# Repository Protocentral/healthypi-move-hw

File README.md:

<div align="center">

</div>

# HealthyPi Move

HealthyPi Move is an open hardware device that lets you track all your vital signs to a high degree of accuracy. But it’s not just another smartwatch with a heart rate monitor. It is a complete vital signs monitoring and recording device on your wrist that can measure electrocardiogram (ECG), photoplethysmogram (PPG), SpO₂, blood pressure (finger-based), EDA/GSR, heart rate variability (HRV), respiration rate, and even body temperature.

The firmware for the HealthyPi Move is available at it's own repository - [HealthyPi Move Firmware](https://github.com/Protocentral/healthypi-move-fw)

HealthyPi Move is now available for pre-order in the ongoing campaign on [Crowd Supply](https://www.crowdsupply.com/protocentral/healthypi-move)

## Repository Contents

* **/pcbs** - All Eagle PCB design files (.brd, .sch)
* **/enclosure** - Enclosure design files

## License Information

This product is open source! Both, our hardware and software are open source and licensed under the following licenses:

Hardware
---------

**All hardware is released under the [CERN-OHL-P v2](https://ohwr.org/cern_ohl_p_v2.txt)** license.

Copyright CERN 2020.

This source describes Open Hardware and is licensed under the CERN-OHL-P v2.

You may redistribute and modify this documentation and make products
using it under the terms of the CERN-OHL-P v2 (https:/cern.ch/cern-ohl).
This documentation is distributed WITHOUT ANY EXPRESS OR IMPLIED
WARRANTY, INCLUDING OF MERCHANTABILITY, SATISFACTORY QUALITY
AND FITNESS FOR A PARTICULAR PURPOSE. Please see the CERN-OHL-P v2
for applicable conditions

Software
--------

**All software is released under the MIT License(http://opensource.org/licenses/MIT).**

THE SOFTWARE IS PROVIDED "AS IS", WITHOUT WARRANTY OF ANY KIND, EXPRESS OR IMPLIED, INCLUDING BUT NOT LIMITED TO THE WARRANTIES OF MERCHANTABILITY, FITNESS FOR A PARTICULAR PURPOSE AND NONINFRINGEMENT. IN NO EVENT SHALL THE AUTHORS OR COPYRIGHT HOLDERS BE LIABLE FOR ANY CLAIM, DAMAGES OR OTHER LIABILITY, WHETHER IN AN ACTION OF CONTRACT, TORT OR OTHERWISE, ARISING FROM, OUT OF OR IN CONNECTION WITH THE SOFTWARE OR THE USE OR OTHER DEALINGS IN THE SOFTWARE.

Documentation
-------------
**All documentation is released under [Creative Commons Share-alike 4.0 International](http://creativecommons.org/licenses/by-sa/4.0/).**

You are free to:

* Share — copy and redistribute the material in any medium or format
* Adapt — remix, transform, and build upon the material for any purpose, even commercially.
The licensor cannot revoke these freedoms as long as you follow the license terms.

Under the following terms:

* Attribution — You must give appropriate credit, provide a link to the license, and indicate if changes were made. You may do so in any reasonable manner, but not in any way that suggests the licensor endorses you or your use.
* ShareAlike — If you remix, transform, or build upon the material, you must distribute your contributions under the same license as the original.

Please check [*LICENSE.md*](LICENSE.md) for detailed license descriptions.

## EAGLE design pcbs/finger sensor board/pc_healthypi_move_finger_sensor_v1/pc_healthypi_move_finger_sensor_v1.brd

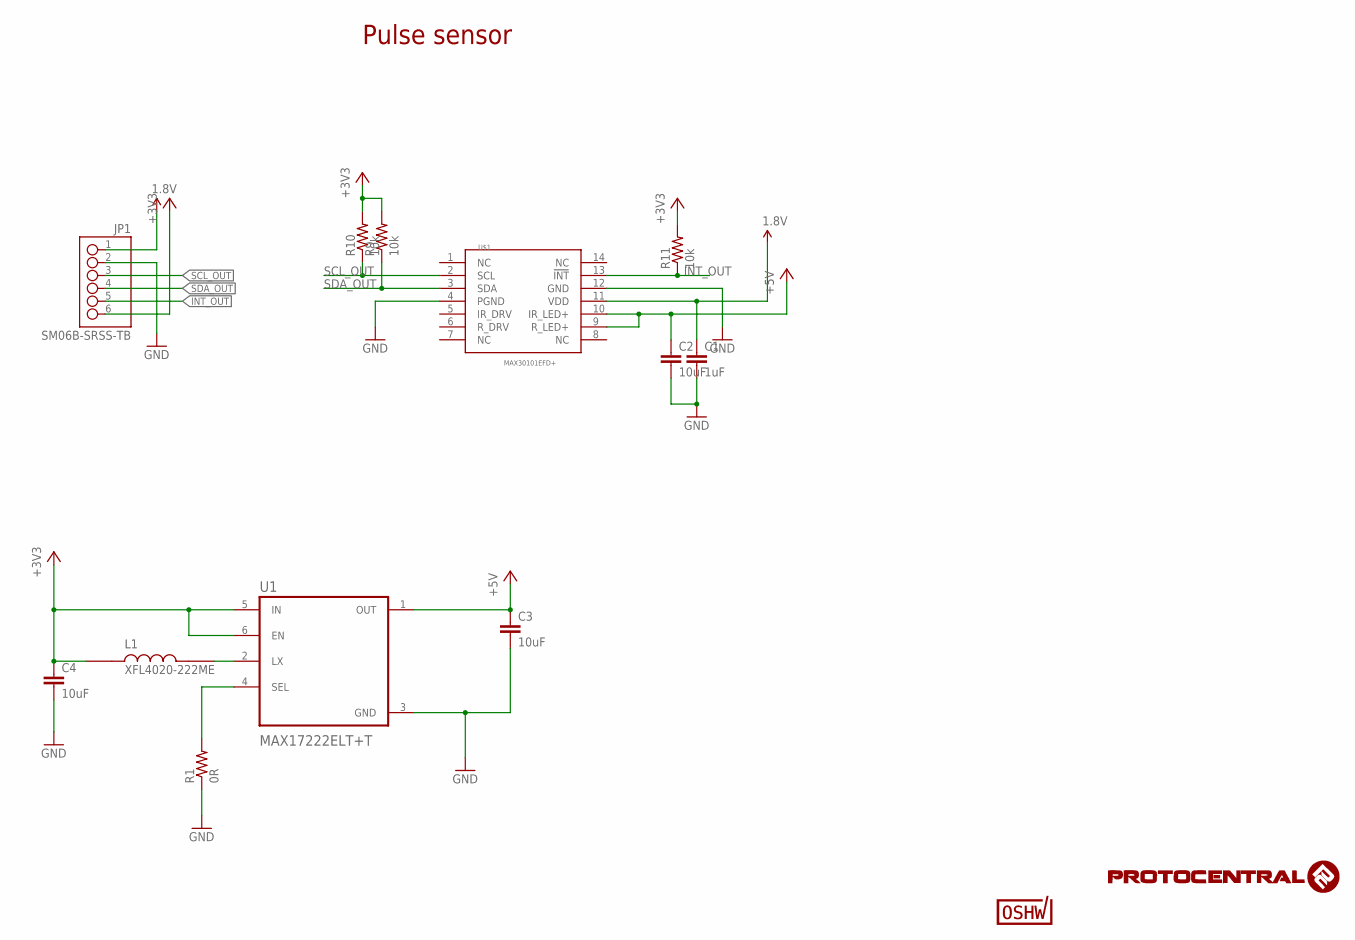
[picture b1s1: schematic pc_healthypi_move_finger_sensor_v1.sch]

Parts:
C1: 1uF; C0402
C2, C3, C4: 10uF; C0402
JP1: SM06B-SRSS-TB
L1: XFL4020-222ME; IND_XFL4020-222ME
R1: 0R; R0402
R9, R10, R11: 10k; R0402
U1: MAX17222ELT+T; SON65P200X200X80-6N
U$1: MAX30101EFD+; OESIP-14
U$9: CERT-SMALL; CERT-SMALL-SILK

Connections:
1.8V: C1.1, JP1.1, U$1.11 (VDD)
+3V3: C4.1, JP1.6, L1.1, R9.2, R10.2, R11.2, U1.5 (IN), U1.6 (EN)
+5V: C2.1, C3.1, U1.1 (OUT), U$1.9 (R_LED+), U$1.10 (IR_LED+)
GND: C1.2, C2.2, C3.2, C4.2, JP1.2, R1.1, U1.3 (GND), U$1.4 (PGND), U$1.12 (GND)
INT_OUT: JP1.5, R11.1, U$1.13 (!INT)
unnamed: R1.2, U1.4 (SEL)
unnamed: L1.2, U1.2 (LX)
SCL_OUT: JP1.3, R10.1, U$1.2 (SCL)
SDA_OUT: JP1.4, R9.1, U$1.3 (SDA)

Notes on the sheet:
Pulse sensor

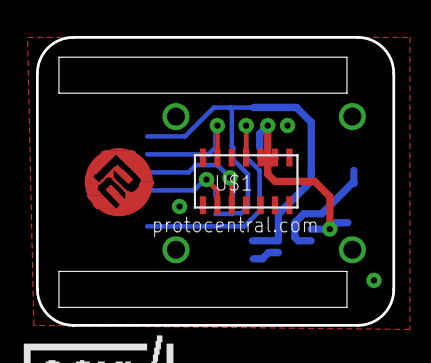
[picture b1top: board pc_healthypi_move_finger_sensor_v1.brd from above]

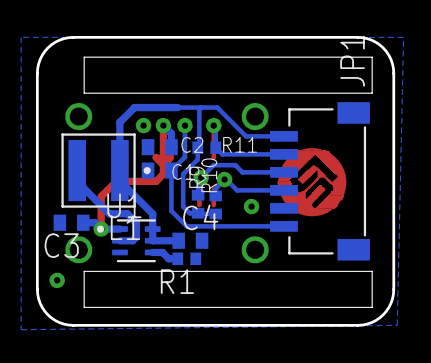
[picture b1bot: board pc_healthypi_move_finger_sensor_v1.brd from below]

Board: 4 copper layers, 19.8 x 16.0 mm, 14 parts (11 on the bottom side), 9 nets.

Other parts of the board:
U$15: PCROUNDLOGO_GOLD

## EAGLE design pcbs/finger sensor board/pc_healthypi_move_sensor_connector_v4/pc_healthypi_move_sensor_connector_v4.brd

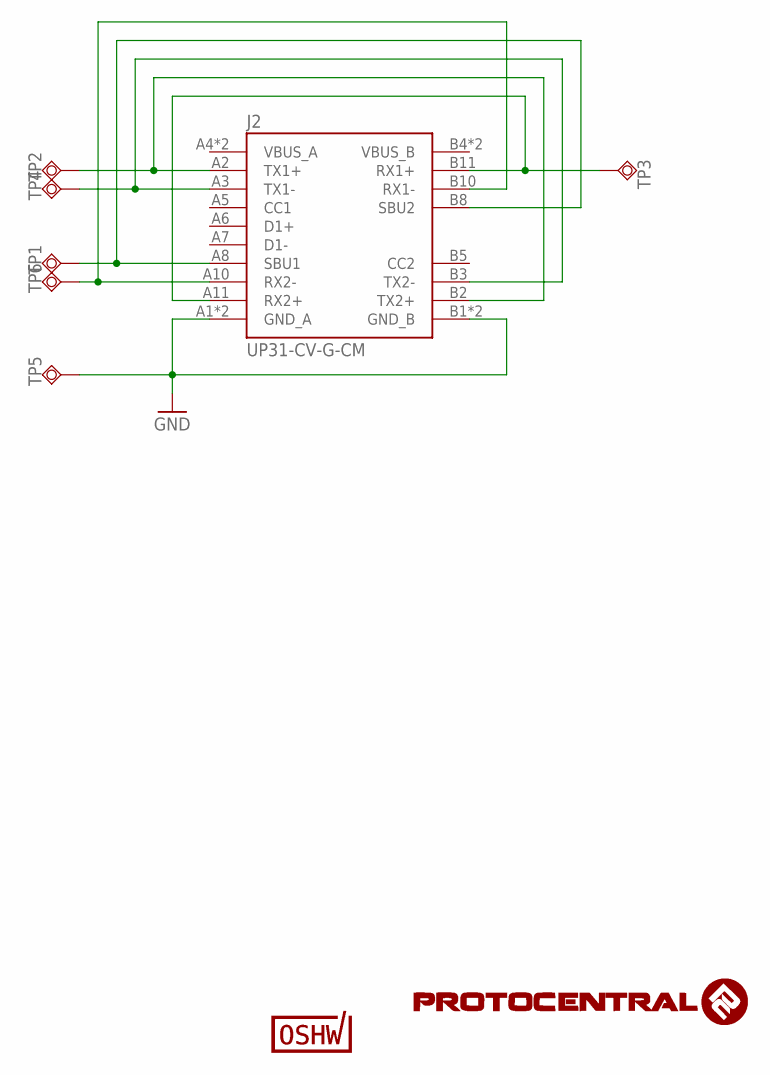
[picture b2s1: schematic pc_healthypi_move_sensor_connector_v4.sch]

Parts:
J2: UP31-CV-G-CM; CUI_UP31-CV-G-CM
TP1, TP2, TP3, TP4, TP5, TP6: TPSQTP10SQ; TP10SQ
U$9: CERT-SMALL; CERT-SMALL-SILK

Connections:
GND: J2.A1 (GND_A), J2.A12 (GND_A), J2.B1 (GND_B), J2.B12 (GND_B), TP5.TP
unnamed: J2.A2 (TX1+), J2.B2 (TX2+), TP2.TP
unnamed: J2.A8 (SBU1), J2.B8 (SBU2), TP1.TP
unnamed: J2.A3 (TX1-), J2.B3 (TX2-), TP4.TP
unnamed: J2.A11 (RX2+), J2.B11 (RX1+), TP3.TP
unnamed: J2.A10 (RX2-), J2.B10 (RX1-), TP6.TP
VBUS_A: J2.A4 (VBUS_A), J2.A9 (VBUS_A)
VBUS_B: J2.B4 (VBUS_B), J2.B9 (VBUS_B)

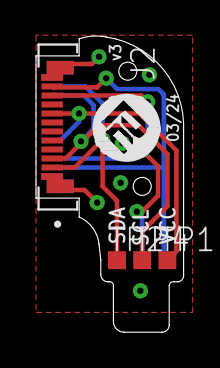
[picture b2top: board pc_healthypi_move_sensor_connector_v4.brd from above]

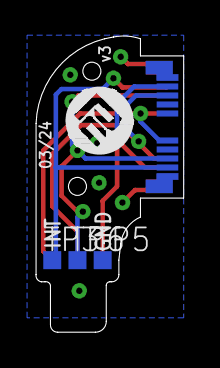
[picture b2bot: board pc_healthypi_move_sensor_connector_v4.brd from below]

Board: 2 copper layers, 8.2 x 16.5 mm, 10 parts (4 on the bottom side), 8 nets.

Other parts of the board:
U$2, U$3: PCROUNDLOGO

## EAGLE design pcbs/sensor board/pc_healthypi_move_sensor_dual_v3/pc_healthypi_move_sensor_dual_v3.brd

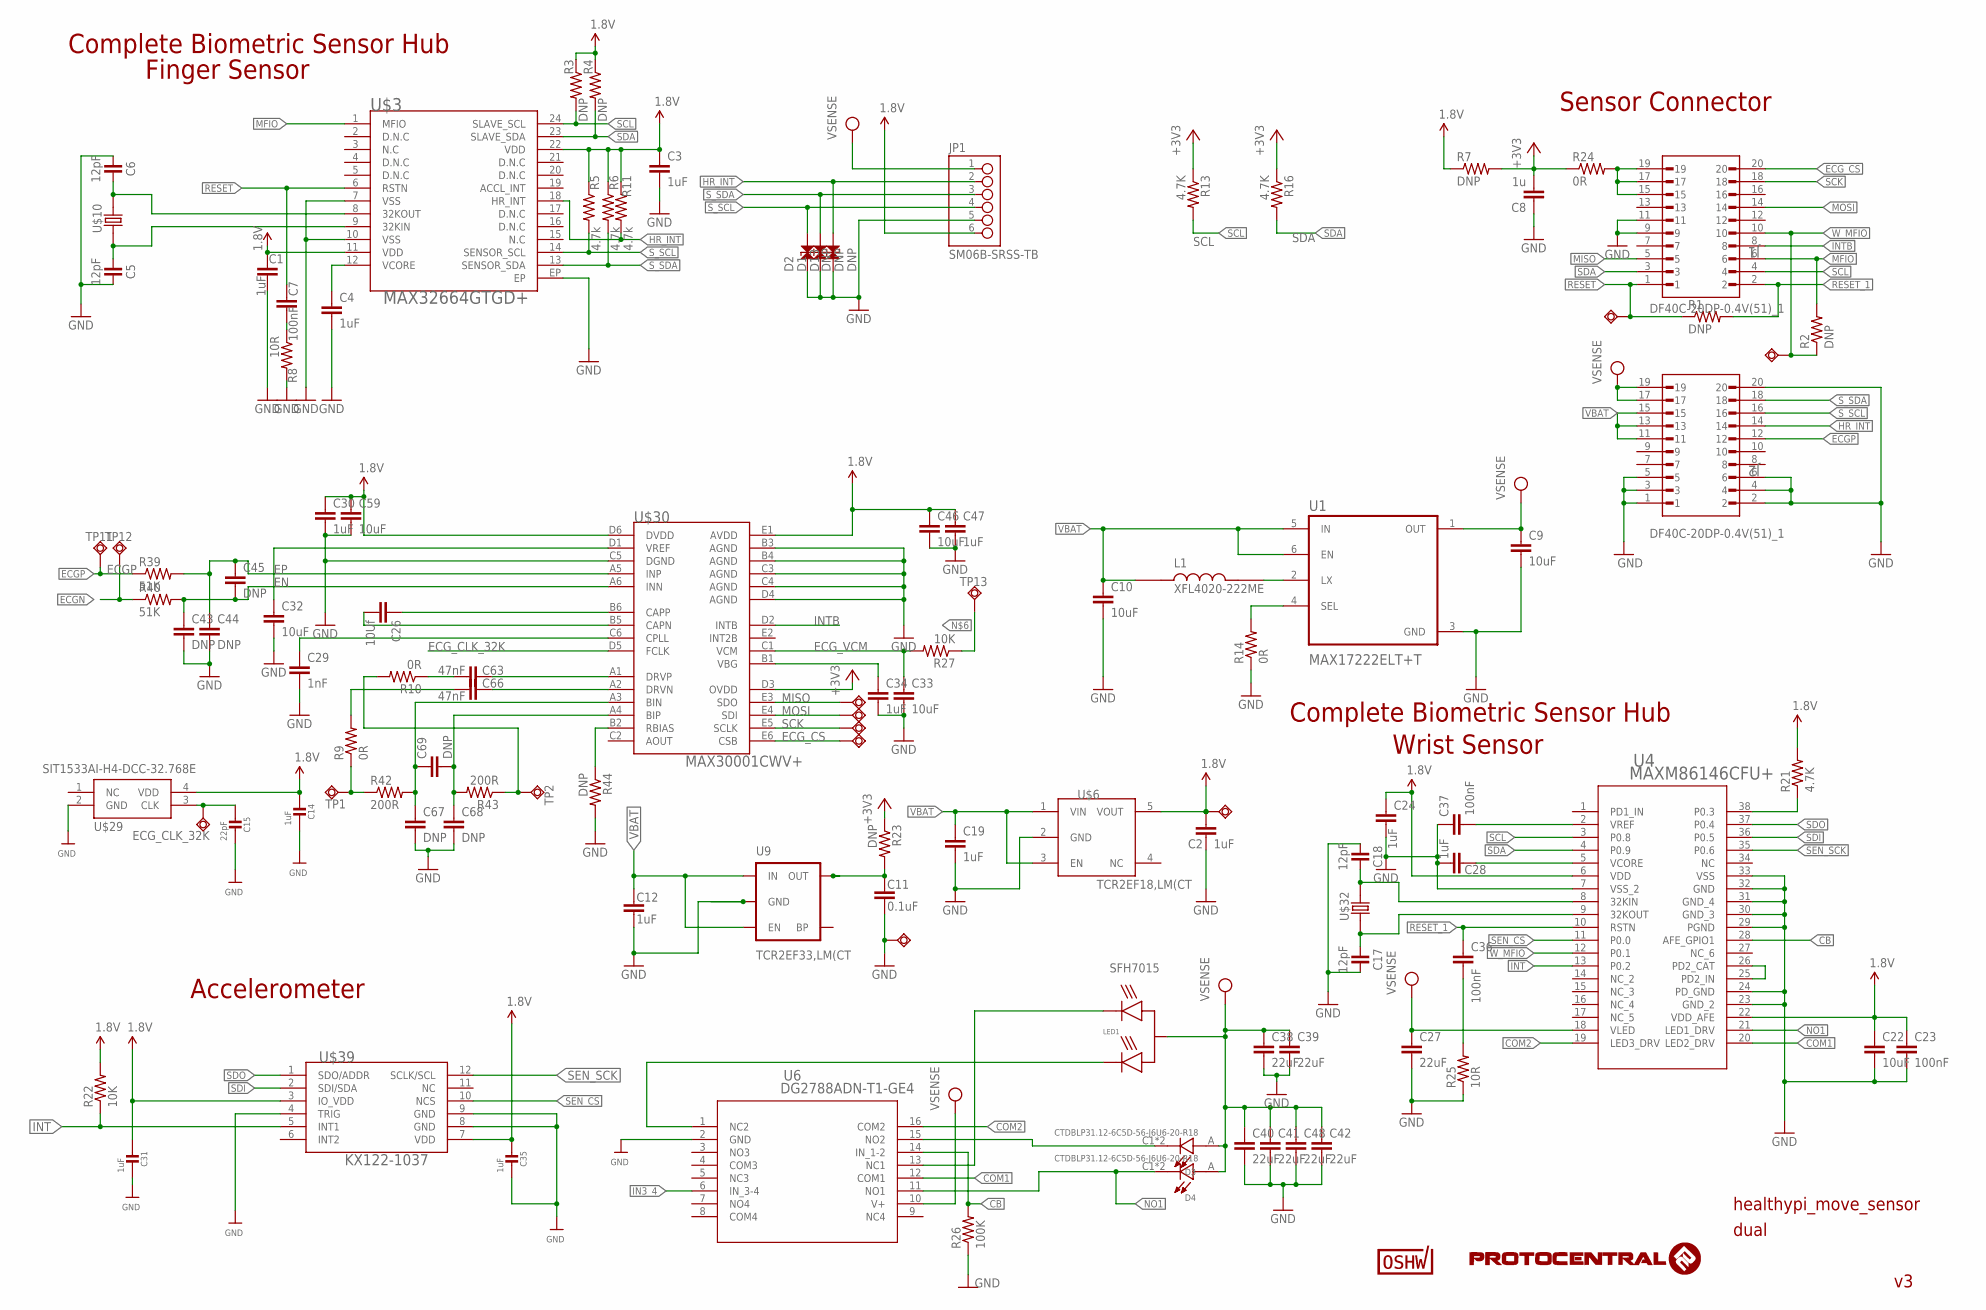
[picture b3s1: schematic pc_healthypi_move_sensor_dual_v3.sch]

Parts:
C1, C2, C3, C4, C19, C24, C28, C30, C34, C47: 1uF; C0402
C5, C6, C17, C18: 12pF; C0402
C7, C23, C36, C37: 100nF; C0402
C8: 1u; C0402
C9, C10, C22, C32, C33, C46, C59: 10uF; C0402
C11: 0.1uF; 0402
C12: 1uF; 0402-TIGHT
C14, C31, C35: 1uF; 0402
C15: 22pF; 0402
C26: 10Uf; C0402
C27, C38, C39, C40, C41, C42, C48: 22uF; C0805
C29: 1nF; C0402
C43, C44, C45, C67, C68, C69: DNP; C0402
C63, C66: 47nF; C0402
D1, D2, D13: DNP; 0402
D3, D4: CTDBLP31.12-6C5D-56-J6U6-20-R18; LED_CTDBLP31.12-6C5D-56-J6U6-20-R18
J1, J2: DF40C-20DP-0.4V(51)_1; HRS_DF40C-20DP-0.4V(51)
JP1: SM06B-SRSS-TB
L1: XFL4020-222ME; IND_XFL4020-222ME
LED1: SFH7015
R1, R2, R3, R4, R7, R23, R44: DNP; 0402-RES
R5, R6, R11: 4.7k; 0402-RES
R8: 10R; 0402-RES
R9, R10, R24: 0R; 0402-RES
R13, R16: 4.7K; 0402-RES
R14: 0R; R0402
R21: 4.7K; R0402
R22: 10K; 0402-RES
R25: 10R; R0402
R26: 100K; R0402
R27: 10K; R0402
R39, R40: 51K; 0402-RES
R42, R43: 200R; 0402-RES
SWIO1, SWIO2, SWIO3, SWIO4, SWIO5, SWIO6, SWIO7, SWIO8, SWIO9: TPSQTP11R; TP11R
TP1, TP2, TP11, TP12, TP13: TPSQTP20SQ; TP20SQ
U1: MAX17222ELT+T; SON65P200X200X80-6N
U4: MAXM86146CFU+; 21-100323A_90-100112A_MXM
U6: DG2788ADN-T1-GE4; MINIQFN-16_VIS
U9: TCR2EF33,LM(CT; SOT23-5
U$3: MAX32664GTGD+; TQFN-24L
U$6: TCR2EF18,LM(CT; SOT95P285X140-5N
U$10, U$32: 520-327-12.5-34B(32.768KHZ); ECX-31B
U$29: SIT1533AI-H4-DCC-32.768E; SIT1533
U$30: MAX30001CWV+; 30WLP
U$39: KX122-1037; KIONIX_KXTJ3-1057
U$48: CERT-SMALL; CERT-SMALL-SILK

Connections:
1.8V: C1.1, C2.1, C3.1, C14.1, C22.1, C23.1, C24.1, C30.1, C31.1, C35.1, C46.1, C47.1, C59.1, JP1.6, R3.1, R4.1, R5.1, R6.1, R7.1, R11.1, R21.2, R22.2, SWIO5.TP, U4.6 (VDD), U4.22 (VDD_AFE), U$3.11 (VDD), U$3.22 (VDD), U$6.5 (VOUT), U$29.4 (VDD), U$30.D6 (DVDD), U$30.E1 (AVDD), U$39.3 (IO_VDD), U$39.7 (VDD)
+3V3: C8.2, R7.2, R13.1, R16.1, R23.1, R24.1, U$30.D3 (OVDD)
BIAZP: R10.2, R43.1, TP2.TP
BIOZN: R9.1, R42.1, TP1.TP
CB: R26.2, U4.28 (AFE_GPIO1), U6.14 (IN_1-2)
CLK_32K: C5.1, U$3.9 (32KIN), U$10.P$1 (1)
CLK_32K1: C17.1, U4.9 (32KOUT), U$32.P$1 (1)
COM1: U4.20 (LED2_DRV), U6.12 (COM1)
COM2: U4.19 (LED3_DRV), U6.16 (COM2)
ECGN: R40.1, TP12.TP
ECGP: J2.12, R39.1, TP11.TP
ECG_CLK_32K: C15.1, SWIO1.TP, U$29.3 (CLK), U$30.D5 (FCLK)
ECG_CS: J1.20, SWIO7.TP, U$30.E6 (CSB)
ECG_VCM: C33.1, R27.2, U$30.C1 (VCM)
EN: C43.1, C45.2, R40.2, U$30.A6 (INN)
EP: C44.1, C45.1, R39.2, U$30.A5 (INP)
EXT_3V3: J1.15, J1.17, J1.19, R24.2
GND: C1.2, C2.2, C3.2, C4.2, C5.2, C6.1, C8.1, C9.2, C10.2, C11.2, C12.2, C14.2, C15.2, C17.2, C18.1, C19.2, C22.2, C23.2, C24.2, C27.2, C28.2, C29.2, C30.2, C31.2, C32.2, C33.2, C34.2, C35.2, C37.1, C38.2, C39.2, C40.2, C41.2, C42.2, C43.2, C44.2, C46.2, C47.2, C48.2, C59.2, C67.2, C68.2, D1.1, D2.1, D13.1, J1.9, J1.11, J2.1, J2.2, J2.3, J2.4, J2.5, J2.6, J2.20, JP1.5, R8.2, R14.1, R25.1, R26.1, R44.2, SWIO6.TP, U1.3 (GND), U4.7 (VSS_2), U4.23 (GND_2), U4.24 (PD_GND), U4.29 (PGND), U4.30 (GND_3), U4.31 (GND_4), U4.32 (GND), U4.33 (VSS), U6.2 (GND), U9.2 (GND), U$3.7 (VSS), U$3.10 (VSS), U$3.EP, U$6.2 (GND), U$29.2 (GND), U$30.B3 (AGND), U$30.B4 (AGND), U$30.C3 (AGND), U$30.C4 (AGND), U$30.C5 (DGND), U$30.D4 (AGND), U$39.4 (TRIG), U$39.8 (GND), U$39.9 (GND)
HR_INT: D13.2, J2.14, JP1.2, R11.2, U$3.18 (HR_INT)
IN3_4: U6.6 (IN_3-4)
INT: R22.1, U4.13 (P0.2), U$39.5 (INT1)
INTB: J1.8, U$30.D2 (INTB)
INT_3V3: C11.1, R23.2, U9.5 (OUT)
MFIO: J1.6, R2.2, U$3.1 (MFIO)
MISO: J1.5, SWIO2.TP, U$30.E3 (SDO)
MOSI: J1.14, SWIO3.TP, U$30.E4 (SDI)
unnamed: C4.1, U$3.12 (VCORE)
unnamed: C7.2, R8.1
unnamed: R14.2, U1.4 (SEL)
unnamed: L1.2, U1.2 (LX)
unnamed: C18.2, U4.8 (32KIN), U$32.P$2 (2)
unnamed: R27.1, TP13.TP
unnamed: U4.25 (PD2_IN), U4.26 (PD2_CAT)
unnamed: C28.1, U4.5 (VCORE)
unnamed: R21.1, U4.38 (P0.3)
unnamed: C37.2, U4.2 (VREF)
unnamed: C36.2, R25.2
unnamed: C66.1, R9.2
unnamed: C63.1, R10.1
unnamed: LED1.4 (IRC), U6.13 (NC1)
unnamed: LED1.2 (RC), U6.1 (NC2)
unnamed: C6.2, U$3.8 (32KOUT), U$10.P$2 (2)
unnamed: D3.C1 (C), D3.C2 (C), U6.15 (NO2)
unnamed: C29.1, U$30.C6 (CPLL)
unnamed: C26.2, U$30.B5 (CAPN)
unnamed: C32.1, U$30.D1 (VREF)
unnamed: C34.1, U$30.B1 (VBG)
unnamed: C26.1, U$30.B6 (CAPP)
unnamed: C63.2, U$30.A1 (DRVP)
unnamed: C66.2, U$30.A2 (DRVN)
unnamed: C67.1, C69.1, R42.2, U$30.A3 (BIN)
unnamed: C68.1, C69.2, R43.2, U$30.A4 (BIP)
unnamed: R44.1, U$30.B2 (RBIAS)
NO1: D4.C1 (C), D4.C2 (C), U4.21 (LED1_DRV), U6.11 (NO1)
RESET: C7.1, J1.1, R1.1, SWIO8.TP, U$3.6 (RSTN)
RESET_1: C36.1, J1.2, R1.2, U4.10 (RSTN)
SCK: J1.18, SWIO4.TP, U$30.E5 (SCLK)
SCL: J1.4, R3.2, R13.2, U4.3 (P0.8), U$3.24 (SLAVE_SCL)
SDA: J1.3, R4.2, R16.2, U4.4 (P0.9), U$3.23 (SLAVE_SDA)
SDI: U4.36 (P0.5), U$39.2 (SDI/SDA)
SDO: U4.37 (P0.4), U$39.1 (SDO/ADDR)
SEN_CS: U4.11 (P0.0), U$39.10 (NCS)
SEN_SCK: U4.35 (P0.6), U$39.12 (SCLK/SCL)
S_SCL: D2.2, J2.16, JP1.4, R5.2, U$3.14 (SENSOR_SCL)
S_SDA: D1.2, J2.18, JP1.3, R6.2, U$3.13 (SENSOR_SDA)
VBAT: C10.1, C12.1, C19.1, J2.11, J2.13, J2.15, L1.1, U1.5 (IN), U1.6 (EN), U9.1 (IN), U9.3 (EN), U$6.1 (VIN), U$6.3 (EN)
VPP: C9.1, C27.1, C38.1, C39.1, C40.1, C41.1, C42.1, C48.1, D3.A, D4.A, J2.17, J2.19, JP1.1, LED1.3 (A), U1.1 (OUT), U4.18 (VLED), U6.10 (V+)
W_MFIO: J1.10, R2.1, SWIO9.TP, U4.12 (P0.1)

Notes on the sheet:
healthypi_move_sensor
Sensor Connector
Complete Biometric Sensor Hub
Accelerometer
SFH7015
dual
Finger Sensor
Wrist Sensor

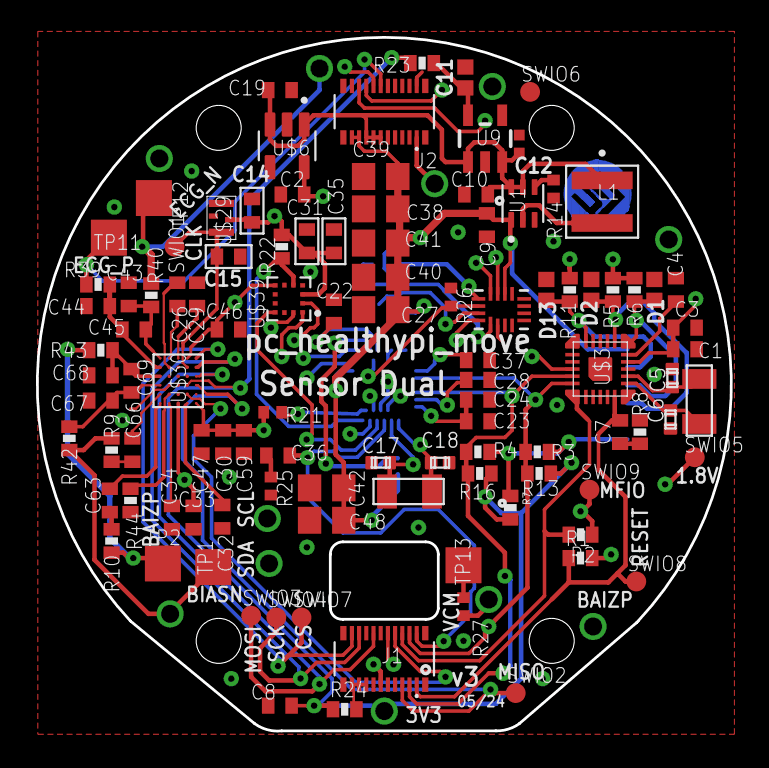
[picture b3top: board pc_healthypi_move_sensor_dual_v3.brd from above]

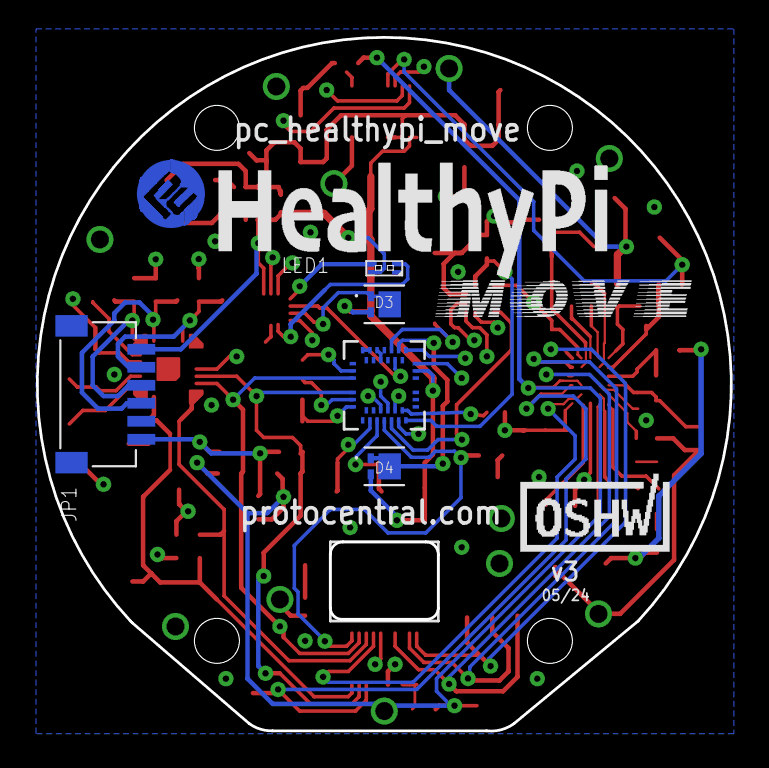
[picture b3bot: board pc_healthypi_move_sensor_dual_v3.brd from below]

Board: 4 copper layers, 38.5 x 38.5 mm, 114 parts (9 on the bottom side), 67 nets.

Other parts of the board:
U$23: HEALTHYPI_MOVE_LOGO_1
U$24: HEALTHYPI_MOVE_LOGO
U$52: PCROUNDLOGO_GOLD

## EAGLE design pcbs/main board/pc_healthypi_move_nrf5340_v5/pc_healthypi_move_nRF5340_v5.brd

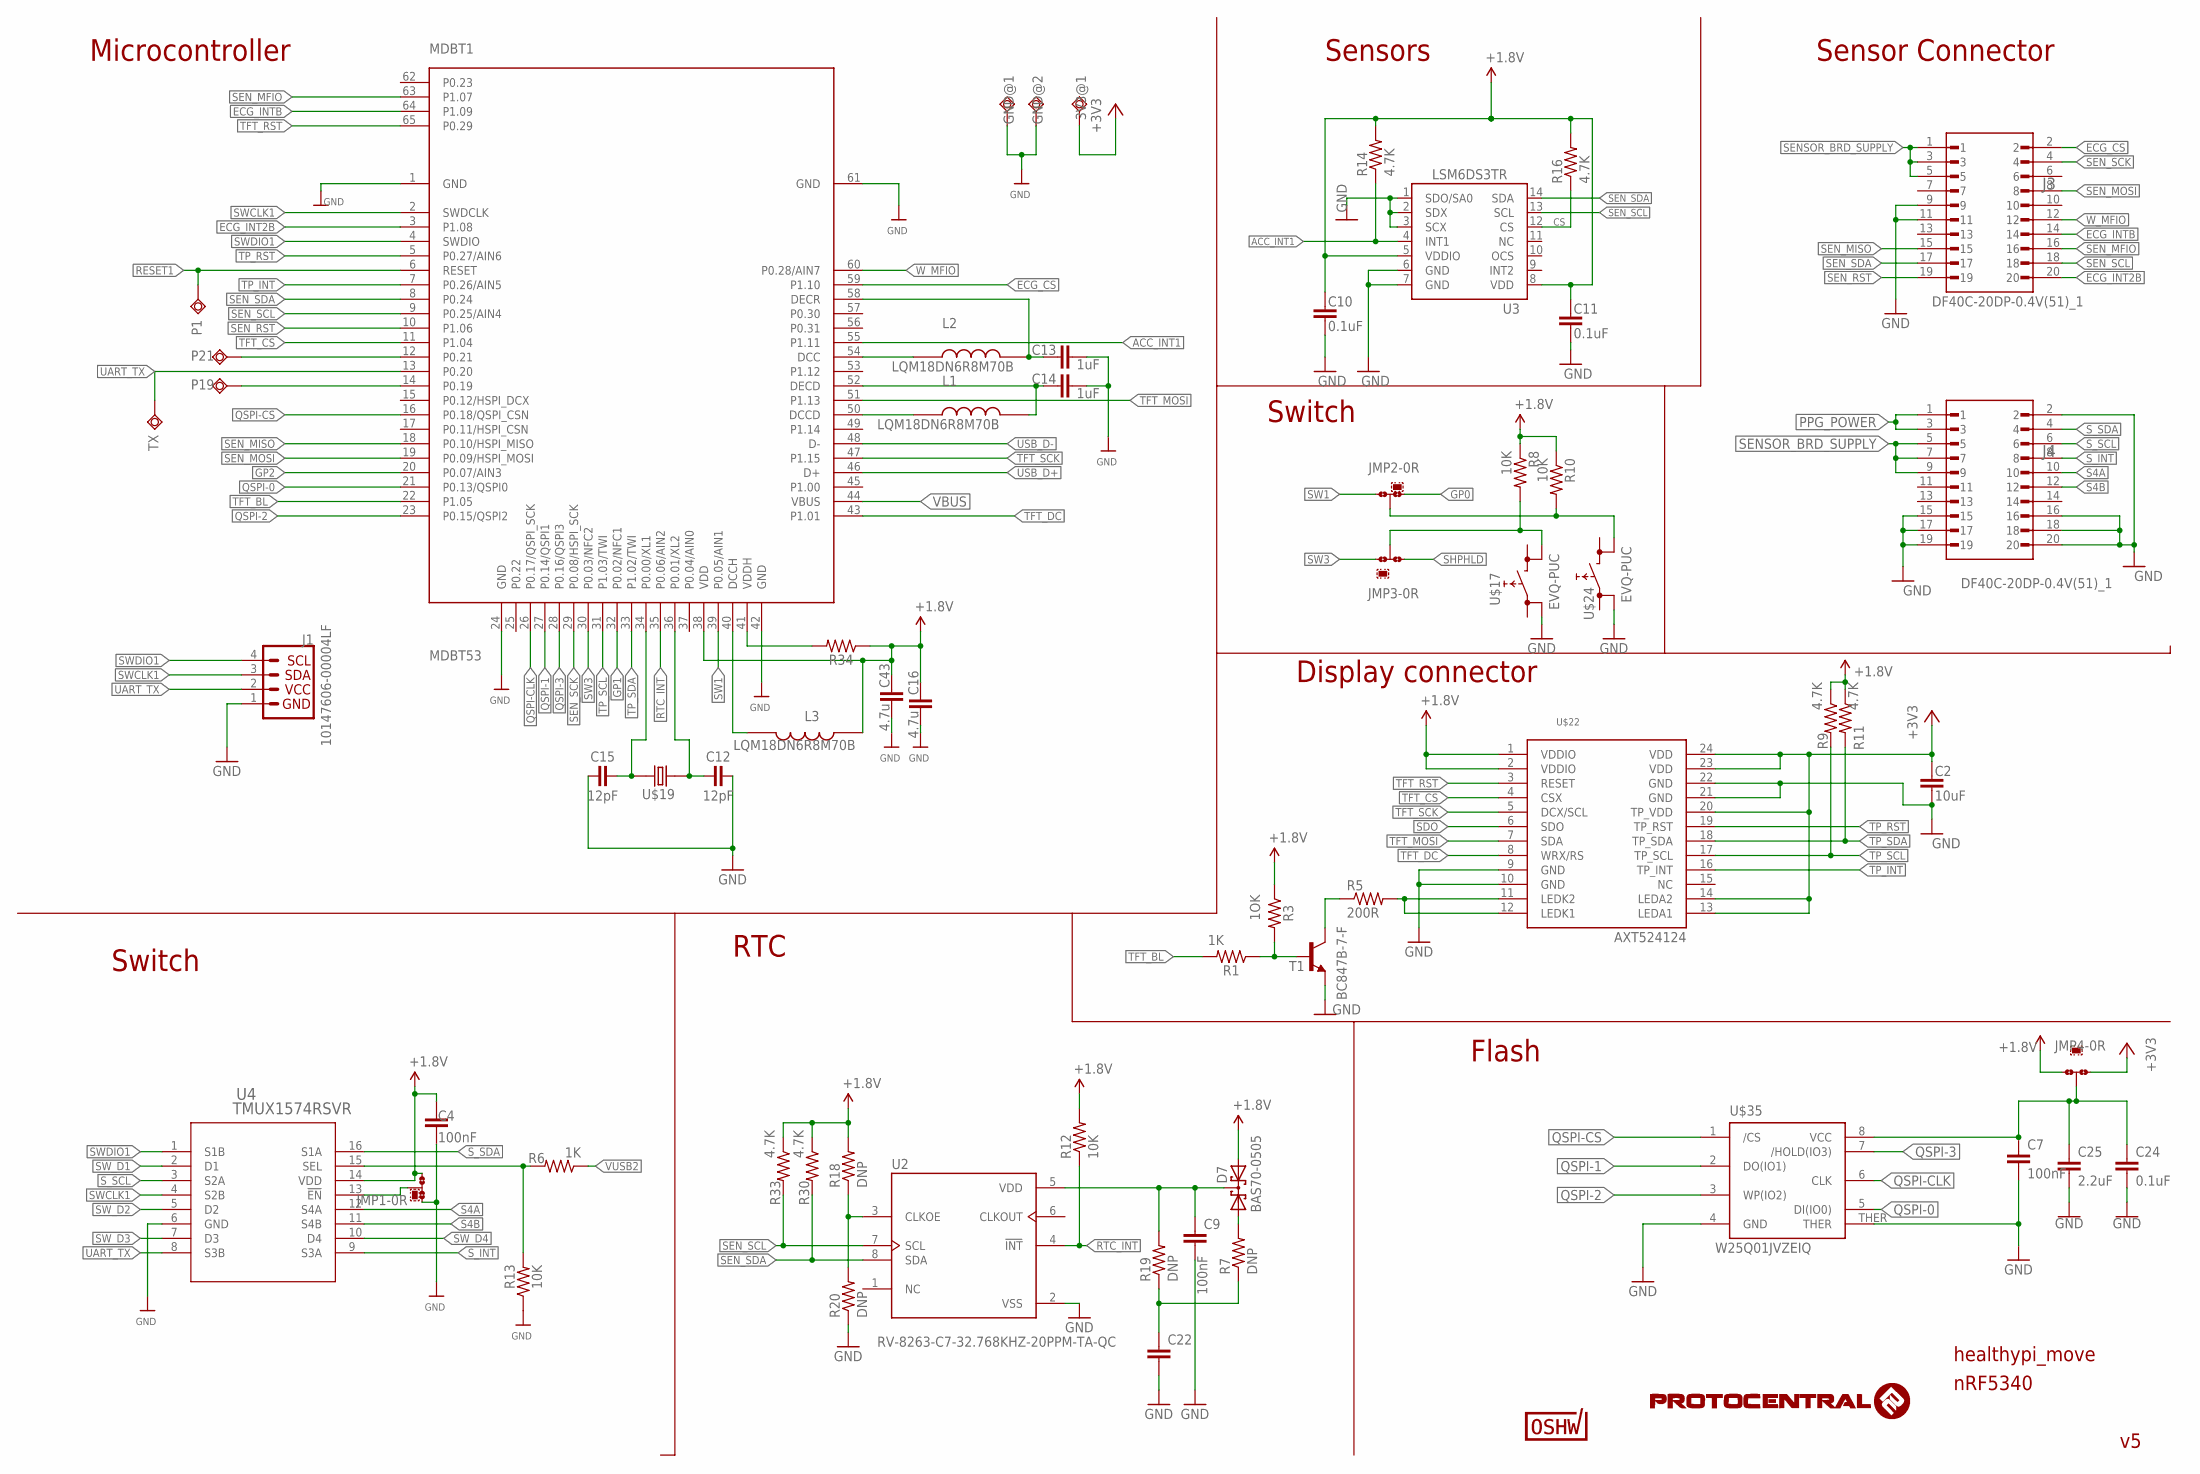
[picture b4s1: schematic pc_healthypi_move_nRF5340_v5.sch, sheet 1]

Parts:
3V3@1: TPSQTP13SQ; TP13SQ
C2: 10uF; 0603@1
C4: 100nF; 0402-TIGHT
C7, C9: 100nF; C0402
C10, C11, C24: 0.1uF; 0402-TIGHT
C12, C15: 12pF; C0402
C13, C14: 1uF; 0402-TIGHT
C16, C43: 4.7u; C0402
C22: C-EUC1210; C1210
C25: 2.2uF; 0402-TIGHT
D7: BAS70-0505; SOT23
GND@1, GND@2: TPSQTP13SQ; TP13SQ
J1: 10147606-00004LF; JST04_1MM_RA
J3, J4: DF40C-20DP-0.4V(51)_1; HRS_DF40C-20DP-0.4V(51)
JMP1, JMP2, JMP3, JMP4: 0R-JUMPB; B0R-JMP
L1, L2, L3: LQM18DN6R8M70B; INDC1608X95N
MDBT1: MDBT53
P1, P19, P21: TPSQTP13SQ; TP13SQ
R1, R3, R34: 200; R0402
R5: 200R; R0402
R6: 1K; 0402-RES
R7, R18, R19, R20: DNP; R0402
R8, R10, R12, R13: 10K; R0402
R9, R11, R14, R16, R30, R33: 4.7K; R0402
T1: BC847B-7-F; SOT23-BEC
TX: TPSQTP13SQ; TP13SQ
U2: RV-8263-C7-32.768KHZ-20PPM-TA-QC; IC_RV-8263-C7-32.768KHZ-20PPM-TA-QC
U3: LSM6DS3TR; LGA14L
U4: TMUX1574RSVR; RSV16_TEX
U$9: CERT-SMALL; CERT-SMALL-SILK
U$17, U$24: EVQ-PUC
U$19: 520-327-12.5-34B(32.768KHZ); ECX-31B
U$22: AXT524124
U$35: W25Q01JVZEIQ; WSON-08

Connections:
+1.8V: C4.1, C10.1, C11.1, C16.1, C43.1, D7.2 (A2), JMP1.3, JMP4.3, L3.1, MDBT1.38 (VDD), R3.1, R8.1, R9.1, R10.1, R11.1, R12.2, R14.2, R16.2, R18.2, R30.1, R33.1, R34.1, U3.5 (VDDIO), U3.8 (VDD), U4.14 (VDD), U$22.1 (VDDIO), U$22.2 (VDDIO); also elsewhere on the board
+3V3: 3V3@1.TP, C2.1, JMP4.1, U$22.13 (LEDA1), U$22.14 (LEDA2), U$22.20 (TP_VDD), U$22.23 (VDD), U$22.24 (VDD); also elsewhere on the board
ACC_INT1: MDBT1.55 (P1.11), R14.1, U3.4 (INT1)
CS: R16.1, U3.12 (CS)
ECG_CS: J3.2, MDBT1.59 (P1.10)
ECG_INT2B: J3.20, MDBT1.3 (P1.08)
ECG_INTB: J3.14, MDBT1.64 (P1.09)
GND: C2.2, C4.2, C7.2, C9.2, C10.2, C11.2, C12.2, C13.2, C14.2, C15.1, C16.2, C22.2, C24.2, C25.2, C43.2, GND@1.TP, GND@2.TP, J1.1, J3.9, J3.11, J4.2, J4.15, J4.16, J4.17, J4.18, J4.19, J4.20, JMP1.1, MDBT1.1 (GND), MDBT1.24 (GND), MDBT1.42 (GND), MDBT1.61 (GND), R13.1, R20.1, T1.E, U2.2 (VSS), U3.1 (SDO/SA0), U3.2 (SDX), U3.3 (SCX), U3.6 (GND), U3.7 (GND), U4.6 (GND), U$17.3 (0), U$22.9 (GND), U$22.10 (GND), U$22.21 (GND), U$22.22 (GND), U$24.3 (0), U$35.4 (GND), U$35.THER; also elsewhere on the board
GP0: JMP2.1; also elsewhere on the board
GP1: MDBT1.32 (P0.02/NFC1); also elsewhere on the board
GP2: MDBT1.20 (P0.07/AIN3); also elsewhere on the board
unnamed: MDBT1.12 (P0.21), P21.TP
unnamed: R5.2, U$22.11 (LEDK2), U$22.12 (LEDK1)
unnamed: R5.1, T1.C
unnamed: R1.1, R3.2, T1.B
unnamed: R6.2, R13.2, U4.15 (SEL)
unnamed: C15.2, MDBT1.34 (P0.00/XL1), U$19.P$2 (2)
unnamed: C9.1, D7.3 (K1K2), R19.2, U2.5 (VDD)
unnamed: R18.1, R20.2, U2.3 (CLKOE)
unnamed: D7.1 (A1), R7.2
unnamed: C22.1, R7.1, R19.1
unnamed: C12.1, MDBT1.36 (P0.01/XL2), U$19.P$1 (1)
unnamed: L3.2, MDBT1.40 (DCCH)
unnamed: JMP1.2, U4.13 (!EN)
unnamed: L1.1, MDBT1.50 (DCCD)
unnamed: C14.1, L1.2, MDBT1.52 (DECD)
unnamed: L2.1, MDBT1.54 (DCC)
unnamed: C13.1, L2.2, MDBT1.58 (DECR)
unnamed: C7.1, C24.1, C25.1, JMP4.2, U$35.8 (VCC)
unnamed: MDBT1.41 (VDDH), R34.2
P19: MDBT1.14 (P0.19), P19.TP
PPG_POWER: J4.1, J4.3; also elsewhere on the board
QSPI-0: MDBT1.21 (P0.13/QSPI0), U$35.5 (DI(IO0))
QSPI-1: MDBT1.27 (P0.14/QSPI1), U$35.2 (DO(IO1))
QSPI-2: MDBT1.23 (P0.15/QSPI2), U$35.3 (WP(IO2))
QSPI-3: MDBT1.28 (P0.16/QSPI3), U$35.7 (/HOLD(IO3))
QSPI-CLK: MDBT1.26 (P0.17/QSPI_SCK), U$35.6 (CLK)
QSPI-CS: MDBT1.16 (P0.18/QSPI_CSN), U$35.1 (/CS)
RESET1: MDBT1.6 (RESET), P1.TP
RTC_INT: MDBT1.35 (P0.06/AIN2), R12.1, U2.4 (!INT)
S4A: J4.10, U4.12 (S4A)
S4B: J4.12, U4.11 (S4B)
SDO: U$22.6 (SDO)
SENSOR_BRD_SUPPLY: J3.1, J3.3, J3.5, J4.5, J4.7, J4.9; also elsewhere on the board
SEN_MFIO: J3.16, MDBT1.63 (P1.07)
SEN_MISO: J3.15, MDBT1.18 (P0.10/HSPI_MISO)
SEN_MOSI: J3.8, MDBT1.19 (P0.09/HSPI_MOSI)
SEN_RST: J3.19, MDBT1.10 (P1.06)
SEN_SCK: J3.4, MDBT1.29 (P0.08/HSPI_SCK)
SEN_SCL: J3.18, MDBT1.9 (P0.25/AIN4), R33.2, U2.7 (SCL), U3.13 (SCL); also elsewhere on the board
SEN_SDA: J3.17, MDBT1.8 (P0.24), R30.2, U2.8 (SDA), U3.14 (SDA); also elsewhere on the board
SHPHLD: JMP3.3; also elsewhere on the board
SW1: JMP2.3, MDBT1.39 (P0.05/AIN1)
SW3: JMP3.1, MDBT1.30 (P0.03/NFC2)
SW11: JMP2.2, R10.2, U$24.2 (1)
SW33: JMP3.2, R8.2, U$17.2 (1)
SWCLK1: J1.3, MDBT1.2 (SWDCLK), U4.4 (S2B)
SWDIO1: J1.4, MDBT1.4 (SWDIO), U4.1 (S1B)
SW_D1: U4.2 (D1); also elsewhere on the board
SW_D2: U4.5 (D2); also elsewhere on the board
SW_D3: U4.7 (D3); also elsewhere on the board
SW_D4: U4.10 (D4); also elsewhere on the board
S_INT: J4.8, U4.9 (S3A)
S_SCL: J4.6, U4.3 (S2A)
S_SDA: J4.4, U4.16 (S1A)
TFT_BL: MDBT1.22 (P1.05), R1.2
TFT_CS: MDBT1.11 (P1.04), U$22.4 (CSX)
TFT_DC: MDBT1.43 (P1.01), U$22.8 (WRX/RS)
TFT_MOSI: MDBT1.51 (P1.13), U$22.7 (SDA)
TFT_RST: MDBT1.65 (P0.29), U$22.3 (RESET)
TFT_SCK: MDBT1.47 (P1.15), U$22.5 (DCX/SCL)
TP_INT: MDBT1.7 (P0.26/AIN5), U$22.16 (TP_INT)
TP_RST: MDBT1.5 (P0.27/AIN6), U$22.19 (TP_RST)
TP_SCL: MDBT1.31 (P1.03/TWI), R9.2, U$22.17 (TP_SCL)
TP_SDA: MDBT1.33 (P1.02/TWI), R11.2, U$22.18 (TP_SDA)
UART_TX: J1.2, MDBT1.13 (P0.20), TX.TP, U4.8 (S3B)
USB_D+: MDBT1.46 (D+); also elsewhere on the board
USB_D-: MDBT1.48 (D-); also elsewhere on the board
VBUS: MDBT1.44 (VBUS); also elsewhere on the board
VUSB2: R6.1; also elsewhere on the board
W_MFIO: J3.12, MDBT1.60 (P0.28/AIN7)

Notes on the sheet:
nRF5340
Sensors
Sensor Connector
Flash
1OK
healthypi_move
Display connector
Switch
Microcontroller
RTC

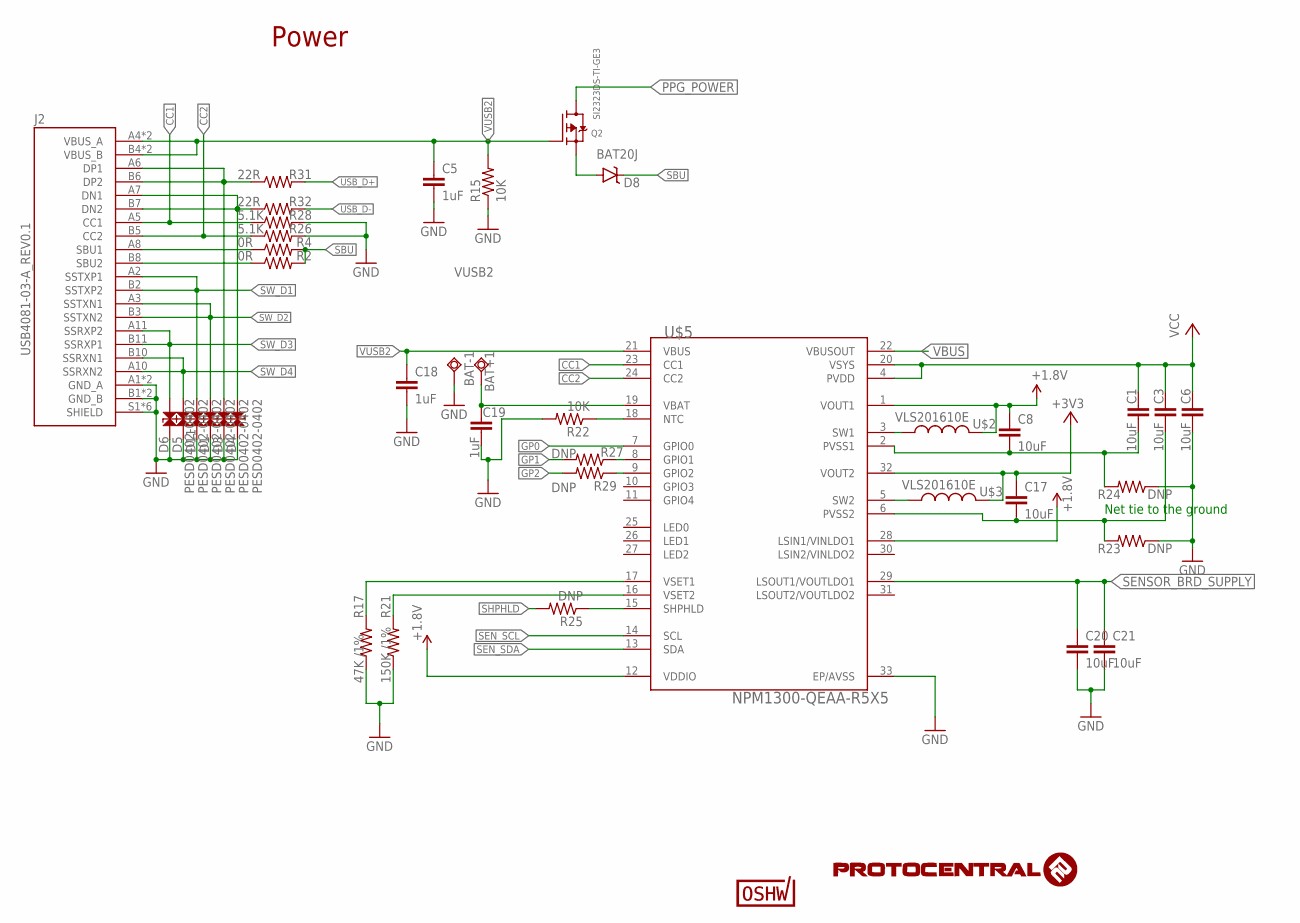
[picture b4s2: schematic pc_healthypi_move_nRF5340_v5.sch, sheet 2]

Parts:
BAT+1: TPSQTP13SQ; TP13SQ
BAT-1: TPSQTP13SQ; TP13SQ
C1, C3, C6, C8, C17, C20, C21: 10uF; 0402-TIGHT
C5, C18, C19: 1uF; 0402-TIGHT
D1, D3, D4, D5, D6, D11: PESD0402-0402; 0402
D8: BAT20J; SOD-323
J2: USB4081-03-A_REV0.1; GCT_USB4081-03-A_REV0.1
Q2: SI2323DS-TI-GE3; SOT23-R
R2, R4: 0R; 0402-RES
R15, R22: 10K; R0402
R17: 47K /1%; 0402-RES
R21: 150K /1%; 0402-RES
R23, R24: DNP; 0402-RES
R25, R27, R29: DNP; R0402
R26, R28: 5.1K; 0402-RES
R31, R32: 22R; 0402-RES
U$2, U$3: VLS201610E
U$5: NPM1300-QEAA-R5X5; QFN32_5X5MC_MCH
U$40: CERT-SMALL; CERT-SMALL-SILK

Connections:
+1.8V: C8.1, U$2.2, U$5.1 (VOUT1), U$5.12 (VDDIO), U$5.28 (LSIN1/VINLDO1); also elsewhere on the board
+3V3: C17.1, U$3.2, U$5.32 (VOUT2); also elsewhere on the board
CC1: J2.A5 (CC1), R28.1, U$5.23 (CC1)
CC2: J2.B5 (CC2), R26.1, U$5.24 (CC2)
GND: BAT-1.TP, C5.2, C6.2, C18.2, C19.2, C20.2, C21.2, D1.1, D3.1, D4.1, D5.1, D6.1, D11.1, J2.A1 (GND_A), J2.A12 (GND_A), J2.B1 (GND_B), J2.B12 (GND_B), J2.S1 (SHIELD), J2.S2 (SHIELD), J2.S3 (SHIELD), J2.S4 (SHIELD), J2.S5 (SHIELD), J2.S6 (SHIELD), R15.1, R17.1, R21.1, R22.2, R23.1, R24.1, R26.2, R28.2, U$5.33 (EP/AVSS); also elsewhere on the board
GP0: U$5.7 (GPIO0); also elsewhere on the board
GP1: R27.2; also elsewhere on the board
GP2: R29.2; also elsewhere on the board
unnamed: J2.B8 (SBU2), R2.1
unnamed: J2.A8 (SBU1), R4.1
unnamed: R17.2, U$5.17 (VSET1)
unnamed: R21.2, U$5.16 (VSET2)
unnamed: R27.1, U$5.8 (GPIO1)
unnamed: C3.2, C17.2, R23.2, U$5.6 (PVSS2)
unnamed: D3.2, J2.A6 (DP1), J2.B6 (DP2), R31.1
unnamed: D4.2, J2.A7 (DN1), J2.B7 (DN2), R32.1
unnamed: U$3.1, U$5.5 (SW2)
unnamed: U$2.1, U$5.3 (SW1)
unnamed: D8.A, Q2.2 (S)
unnamed: BAT+1.TP, C19.1, U$5.19 (VBAT)
unnamed: R29.1, U$5.9 (GPIO2)
unnamed: C1.2, C8.2, R24.2, U$5.2 (PVSS1)
unnamed: R22.1, U$5.18 (NTC)
unnamed: R25.1, U$5.15 (SHPHLD)
PPG_POWER: Q2.3 (D); also elsewhere on the board
SBU: D8.C, R2.2, R4.2
SENSOR_BRD_SUPPLY: C20.1, C21.1, U$5.29 (LSOUT1/VOUTLDO1); also elsewhere on the board
SEN_SCL: U$5.14 (SCL); also elsewhere on the board
SEN_SDA: U$5.13 (SDA); also elsewhere on the board
SHPHLD: R25.2; also elsewhere on the board
SW_D1: D11.2, J2.A2 (SSTXP1), J2.B2 (SSTXP2); also elsewhere on the board
SW_D2: D1.2, J2.A3 (SSTXN1), J2.B3 (SSTXN2); also elsewhere on the board
SW_D3: D6.2, J2.A11 (SSRXP2), J2.B11 (SSRXP1); also elsewhere on the board
SW_D4: D5.2, J2.A10 (SSRXN2), J2.B10 (SSRXN1); also elsewhere on the board
USB_D+: R31.2; also elsewhere on the board
USB_D-: R32.2; also elsewhere on the board
VBUS: U$5.22 (VBUSOUT); also elsewhere on the board
VCC: C1.1, C3.1, C6.1, U$5.4 (PVDD), U$5.20 (VSYS)
VUSB2: C5.1, C18.1, J2.A4 (VBUS_A), J2.A9 (VBUS_A), J2.B4 (VBUS_B), J2.B9 (VBUS_B), Q2.1 (G), R15.2, U$5.21 (VBUS); also elsewhere on the board

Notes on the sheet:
Power
Net tie to the ground

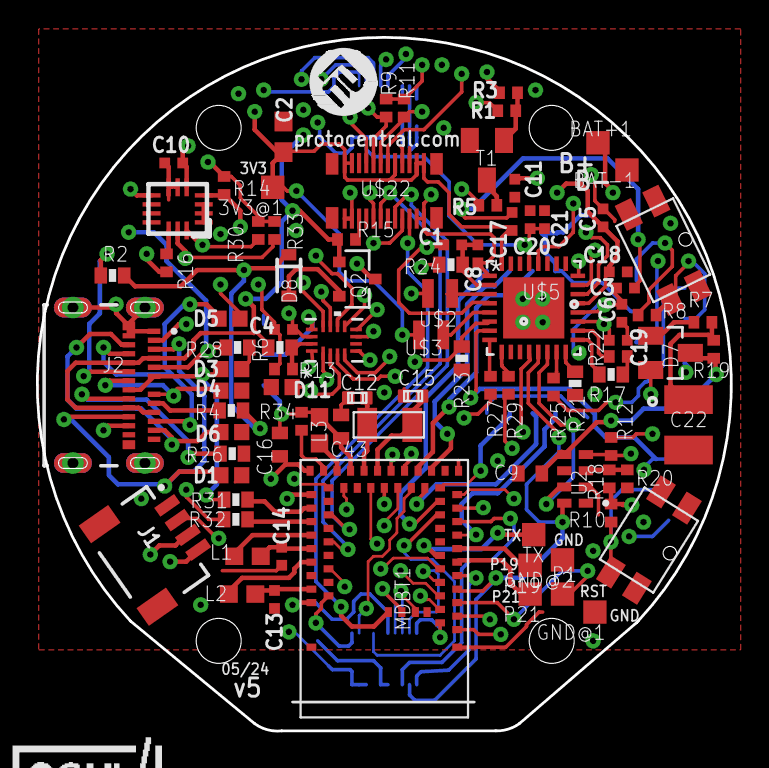
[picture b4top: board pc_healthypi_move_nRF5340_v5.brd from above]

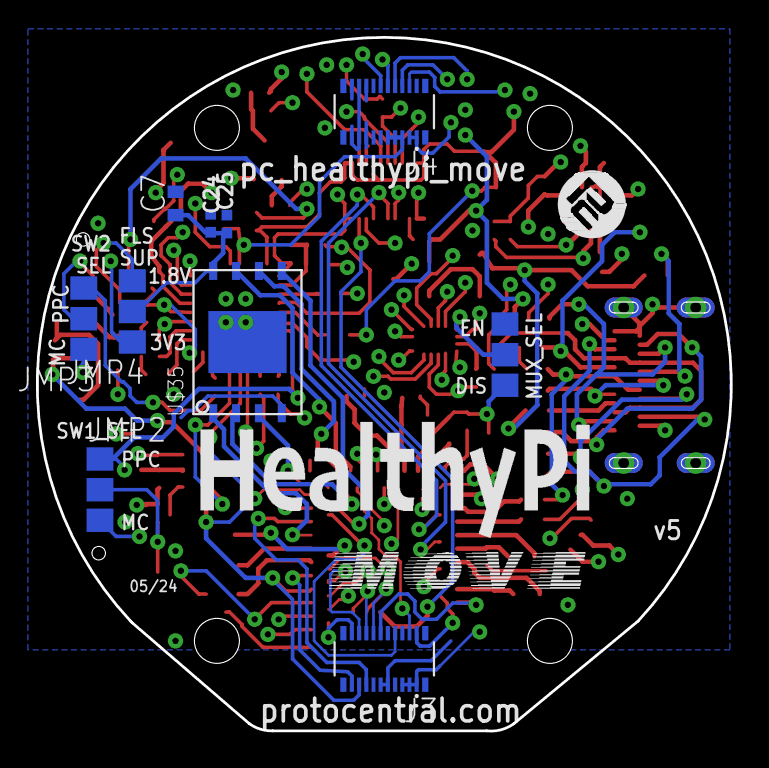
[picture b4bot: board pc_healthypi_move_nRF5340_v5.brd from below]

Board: 4 copper layers, 38.5 x 38.5 mm, 107 parts (13 on the bottom side), 100 nets.

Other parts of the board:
U$6: HEALTHYPI_MOVE_LOGO_1
U$10, U$36: PCROUNDLOGO
U$13: HEALTHYPI_MOVE_LOGO

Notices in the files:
README.md:
CC-BY-SA-4.0
parts and their libraries:
microbuilder: This work is placed in the public domain, and may be freely used for commercial and non-commercial work with the following conditions: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
SparkFun-Aesthetics: Licensing: Creative Commons ShareAlike 4.0 International - https://creativecommons.org/licenses/by-sa/4.0
